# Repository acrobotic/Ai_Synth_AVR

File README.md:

## Ai\_Synth\_AVR

PCB design files (EAGLE) and example Arduino firmware for a MIDI Synthesizer
based on the ATMega328 MCU.

## Description

For more details, check out the product page at:

   * https://acrobotic.com/kit-00002

Designed by ACROBOTIC Industries.  Please consider buying products from us to 
help fund future Open-Source projects like this! We’ll always put our best 
effort in every project, and release all our design files and code for you to 
use. 

## License

Released under the Creative Commons Attribution, Share-Alike license. Please 
check LICENSE.txt for more information. All text above must be included in any 
redistribution.

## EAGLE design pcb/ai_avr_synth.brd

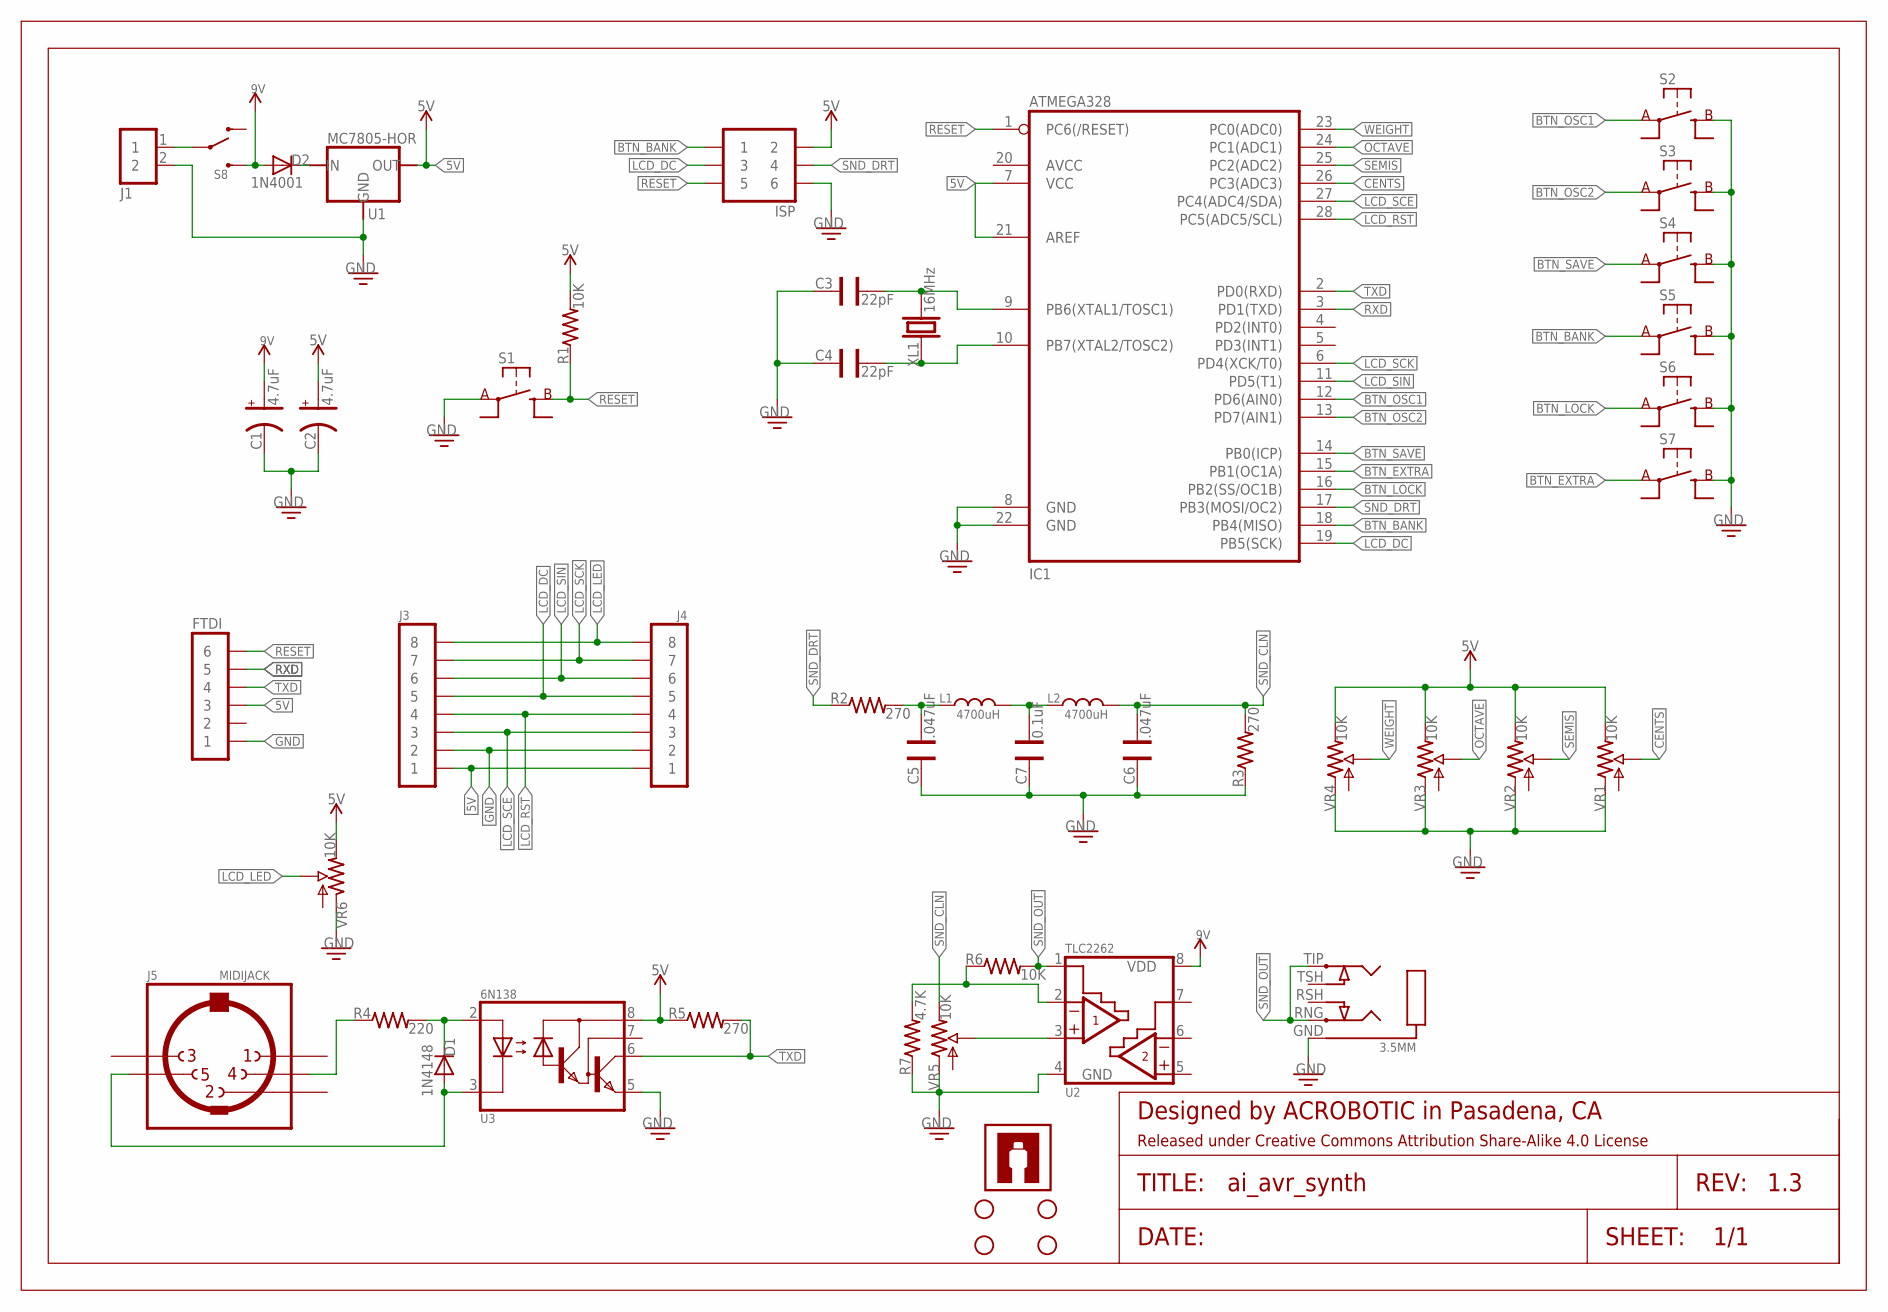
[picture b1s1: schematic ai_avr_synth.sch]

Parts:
3.5MM: STEREOJACKSJ1-351XNG; SJ1-351XNG
C1, C2: 4.7uF; CAP-POL-025X50
C3, C4: 22pF; CAP-025X050
C5, C6: .047uF; CAP-025X050
C7: 0.1uF; CAP-025X050
D1: 1N4148; TH-1N914
D2: 1N4001; TH-1N914
FRAME1: FRAME-LETTER; CREATIVE-COMMONS
FTDI: 1X06
IC1: ATMEGA328P-PDIP; DIL28
ISP: 2X03
J1: 1X02ST; 1X02-ST
J3, J4: 1X08
J5: MIDIJACK; CP-2350
L1, L2: 4700uH; RLB0912
R1, R6: 10K; RES-AXIAL-0.4
R2, R3, R5: 270; RES-AXIAL-0.4
R4: 220; RES-AXIAL-0.4
R7: 4.7K; RES-AXIAL-0.4
S1, S2, S3, S4, S5, S6, S7: SW-SPSTTH06X06; SW-SPST-TH06X06
S8: SW-SPDTTH; SW-SPDT-TH
STANDOFF5, STANDOFF6, STANDOFF7, STANDOFF8: STAND-OFF4; STAND-OFF-4
U1: MC7805-HOR; TO220
U2: TLC2262; DIL08
U3: 6N138; DIL08
U$5: AI-LOGOXS; AI-LOGO-XS
VR1, VR2, VR3, VR4, VR5: 10K; POT-09X09
VR6: 10K; POT-05X05
XL1: 16MHz; HC49S

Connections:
5V: C2.A, FTDI.3, IC1.7 (VCC), IC1.21 (AREF), ISP.2, J3.1, J4.1, R1.P$2 (2), R5.P$1 (1), U1.OUT, U3.8 (VCC), VR1.P$1 (E), VR2.P$1 (E), VR3.P$1 (E), VR4.P$1 (E), VR6.1 (E)
9V: C1.A, D2.A, S8.3 (L2), U2.8 (VDD)
BTN_BANK: IC1.18 (PB4(MISO)), ISP.1, S5.A@1 (A)
BTN_EXTRA: IC1.15 (PB1(OC1A)), S7.A@1 (A)
BTN_LOCK: IC1.16 (PB2(SS/OC1B)), S6.A@1 (A)
BTN_OSC1: IC1.12 (PD6(AIN0)), S2.A@1 (A)
BTN_OSC2: IC1.13 (PD7(AIN1)), S3.A@1 (A)
BTN_SAVE: IC1.14 (PB0(ICP)), S4.A@1 (A)
CENTS: IC1.26 (PC3(ADC3)), VR1.P$2 (S)
GND: 3.5MM.GND, C1.C, C2.C, C3.2, C4.2, C5.2, C6.2, C7.2, FTDI.1, IC1.8 (GND), IC1.22 (GND), ISP.6, J1.2, J3.2, J4.2, R3.P$1 (1), R7.P$1 (1), S1.A@1 (A), S2.B@1 (B), S3.B@1 (B), S4.B@1 (B), S5.B@1 (B), S6.B@1 (B), S7.B@1 (B), U1.GND, U2.4 (GND), U3.5 (GND), VR1.P$3 (A), VR2.P$3 (A), VR3.P$3 (A), VR4.P$3 (A), VR5.P$3 (A), VR6.3 (A)
LCD_DC: IC1.19 (PB5(SCK)), ISP.3, J3.5, J4.5
LCD_LED: J3.8, J4.8, VR6.2 (S)
LCD_RST: IC1.28 (PC5(ADC5/SCL)), J3.4, J4.4
LCD_SCE: IC1.27 (PC4(ADC4/SDA)), J3.3, J4.3
LCD_SCK: IC1.6 (PD4(XCK/T0)), J3.7, J4.7
LCD_SIN: IC1.11 (PD5(T1)), J3.6, J4.6
unnamed: J5.4, R4.P$1 (1)
unnamed: C4.1, IC1.10 (PB7(XTAL2/TOSC2)), XL1.1
unnamed: C3.1, IC1.9 (PB6(XTAL1/TOSC1)), XL1.2
unnamed: J1.1, S8.2 (COM)
unnamed: D2.C, U1.IN
unnamed: D1.C, R4.P$2 (2), U3.2 (A)
unnamed: D1.A, J5.5, U3.3 (C)
unnamed: U2.3 (1IN+), VR5.P$2 (S)
unnamed: C5.1, L1.2, R2.P$2 (2)
unnamed: C7.1, L1.1, L2.2
unnamed: R6.P$1 (1), R7.P$2 (2), U2.2 (1IN-)
OCTAVE: IC1.24 (PC1(ADC1)), VR3.P$2 (S)
RESET: FTDI.6, IC1.1 (PC6(/RESET)), ISP.5, R1.P$1 (1), S1.B@1 (B)
RXD: FTDI.5, IC1.3 (PD1(TXD))
SEMIS: IC1.25 (PC2(ADC2)), VR2.P$2 (S)
SND_CLN: C6.1, L2.1, R3.P$2 (2), VR5.P$1 (E)
SND_DRT: IC1.17 (PB3(MOSI/OC2)), ISP.4, R2.P$1 (1)
SND_OUT: 3.5MM.RNG, 3.5MM.TIP, R6.P$2 (2), U2.1 (1OUT)
TXD: FTDI.4, IC1.2 (PD0(RXD)), R5.P$2 (2), U3.6 (VO)
WEIGHT: IC1.23 (PC0(ADC0)), VR4.P$2 (S)

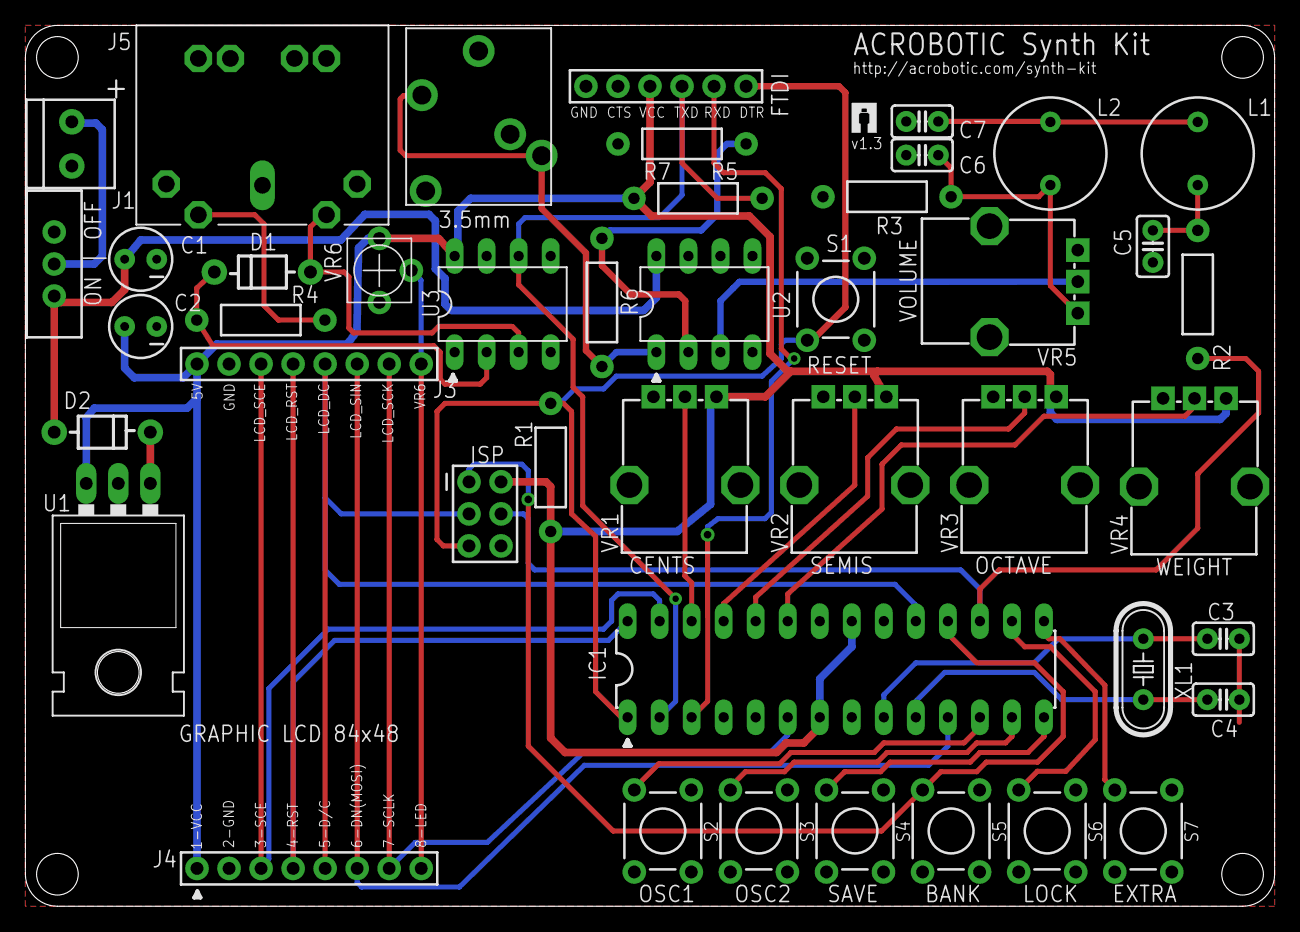
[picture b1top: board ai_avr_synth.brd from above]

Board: 2 copper layers, 99.1 x 69.8 mm, 50 parts (0 on the bottom side), 36 nets.

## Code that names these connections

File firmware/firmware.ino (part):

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#define OSC1_PIN		11
#define EXTRA_PIN		9

#define CENTS_PIN   A3
#define SEMIS_PIN   A2
#define OCTAVE_PIN  A1
#define WEIGHT_PIN  A0

#define LFOFREQ_PIN  A3
#define LFOAMNT_PIN  A2
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
//Detune settings
double centMultiplier = 0; //the number multiplied to the frequency to create cent shift
double cents = 0; //number of cents
int octaveShift = 0;
int semis = 0;
byte phase = 0;

//LFO Settings
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			case MENU_NORM:
			if(!settingsLocked[MENU_NORM])
			{
				cents = map(analogRead(CENTS_PIN),ADC_MIN,ADC_MAX,-CENTS_MAX,CENTS_MAX);  //from -100 to 100 cents
				semis = map(analogRead(SEMIS_PIN),ADC_MIN,ADC_MAX,-12,12);  //from -12 to 12 semitone
				octaveShift = map(analogRead(OCTAVE_PIN),ADC_MIN,ADC_MAX,-OCT_MAX, OCT_MAX);  //from -2 to 2 octaves
				weight2 = map(analogRead(WEIGHT_PIN),ADC_MAX,ADC_MIN,WEIGHT_MAX,0);  //weight of osc2 in summation
			}
			break;
			
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			case MENU_EXTRA:
			if(!settingsLocked[MENU_EXTRA])
			{
				//phase = map(analogRead(OCTAVE_PIN), ADC_MIN, ADC_MAX, -127, 127);
				arpSpeed = map(analogRead(WEIGHT_PIN),ADC_MIN,ADC_MAX,500,50); //arpSpeed is measured in milliseconds not hertz
			}
			break;
		}
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
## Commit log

2013-10-02 first commit.
2013-10-02 Revisions on LCD orientation, and positioning of switches/pots.
2013-10-03 updated index.html
2013-10-03 Adding gerbers, firmware. Updated README and index.
2013-10-03 adding static files: firmware.zip and pdf schematic.
2013-10-04 Finalized BOM.
2013-10-04 Final version of BOM.xls
2013-10-04 Updating libraries
2013-10-04 changes to schematic fonts, and audiojack pad names
2013-10-04 changes to schematic fonts
2013-10-04 minor change to silkscreen.
2013-10-05 Minor formatting change of BOM.
2013-10-08 Fixed typo in BOM
2013-10-16 Updated components to use the latest libraries. Had to redo a few traces (nothing major)
2013-11-21 New version with modifications discussed with @humanHardDrive
2013-11-25 BOM updated.
2013-11-25 Updating pcb schematic and link on project description
2014-01-07 Update firmware.ino
    Updated MIDI code with CC program controls.
2014-02-06 updated a few components
2014-02-06 updating schematic
2014-02-26 Update firmware.ino
    Updates in optimization and error fixes
2014-02-28 Update firmware.ino
    Final version. Bank switching working. Very well optimized.
2014-03-19 Release Version
2014-03-27 fixed trimmer footprint
2014-04-30 Updated BOM
2014-06-19 adding guide
2014-06-19 working on guide
2014-06-19 moving files around
2014-07-28 updating
2014-07-29 updating guide
2014-12-17 updaing guide
2015-09-29 adding additional licensing information
2015-09-29 adding schematic pdf
2015-10-16 Rename Assembly_Guide.md to assembly_guide.md
2015-10-27 updating guides
2015-10-29 updating guide and BOM to remove C8

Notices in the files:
firmware/firmware.ino:
The contents of this file are licensed under a Creative Commons Attribution-ShareAlike 3.0
Unported License http://creativecommons.org/licenses/by-sa/3.0/.
parts and their libraries:
Ai_Miscellany: Attribution Share-Alike 4.0 License
Ai_Miscellany: https://creativecommons.org/licenses/by-sa/4.0
Ai_Miscellany: Released under Creative Commons Attribution Share-Alike 4.0 License
